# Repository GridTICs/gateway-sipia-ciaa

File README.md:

# Proyecto Final UTN-FRM - Ingeniería Electrónica

_El proyecto se basa en la creación de un gateway que enlaza una red de sensores con un servidor de internet. El README está en su versión beta._ 🚀

_Estas instrucciones te permitirán obtener una copia del proyecto en funcionamiento en tu CIAA para propósitos de desarrollo y pruebas._

*Todo se ha realizado en base al proyecto EDU-CIAA.*

*Se puede encontrar información correspondiente en su página:*

http://www.proyecto-ciaa.com.ar

### Pre-requisitos 📋

> ```
> Tener instalado el "Embedded IDE", GUI de programación de la EDU-CIAA, creada por Martin Ribelotta - El proyecto está creado en dicha aplicación corriendo en Windows 10 x64.
> ```
>

*Dicho software se puede obtener del siguiente link:*

https://github.com/martinribelotta/embedded-ide-builder/releases/tag/v0.6

*En el mismo ya se encuentran las herramientas necesarias para grabar la EDU-CIAA (NXP en mi caso).*

### Instalación 🔧

_Una serie de ejemplos paso a paso que te dice lo que debes ejecutar para tener un entorno de desarrollo ejecutandose_

_Dí cómo será ese paso_

```
Da un ejemplo
```

_Y repite_

```
hasta finalizar
```

_Finaliza con un ejemplo de cómo obtener datos del sistema o como usarlos para una pequeña demo_-

## Ejecutando las pruebas ⚙️

_Explica como ejecutar las pruebas automatizadas para este sistema_

### Analice las pruebas end-to-end 🔩

_Explica que verifican estas pruebas y por qué_

```
Da un ejemplo
```

### Y las pruebas de estilo de codificación ⌨️

_Explica que verifican estas pruebas y por qué_

```
Da un ejemplo
```

## Deployment 📦

_Agrega notas adicionales sobre como hacer deploy_

## Construido con 🛠️

_[CIAA Embedded IDE](https://github.com/martinribelotta/embedded-ide-builder/releases/tag/v0.6) - El IDE de programación utilizado.

## Contribuyendo 🖇️

Por el momento el proyecto es de carácter privado, pero será abierto cuando la versión beta 1.0 esté finalizada.

## Wiki 📖

Puedes encontrar mucho más de cómo utilizar este proyecto en nuestra [Wiki](https://github.com/tu/proyecto/wiki)

## Autores ✒️

_Menciona a todos aquellos que ayudaron a levantar el proyecto desde sus inicios_

* **Lucas Escribano** - [harrylae](https://github.com/harrylae)
* **Rodrigo Gonzalez** 

## Expresiones de Gratitud 🎁

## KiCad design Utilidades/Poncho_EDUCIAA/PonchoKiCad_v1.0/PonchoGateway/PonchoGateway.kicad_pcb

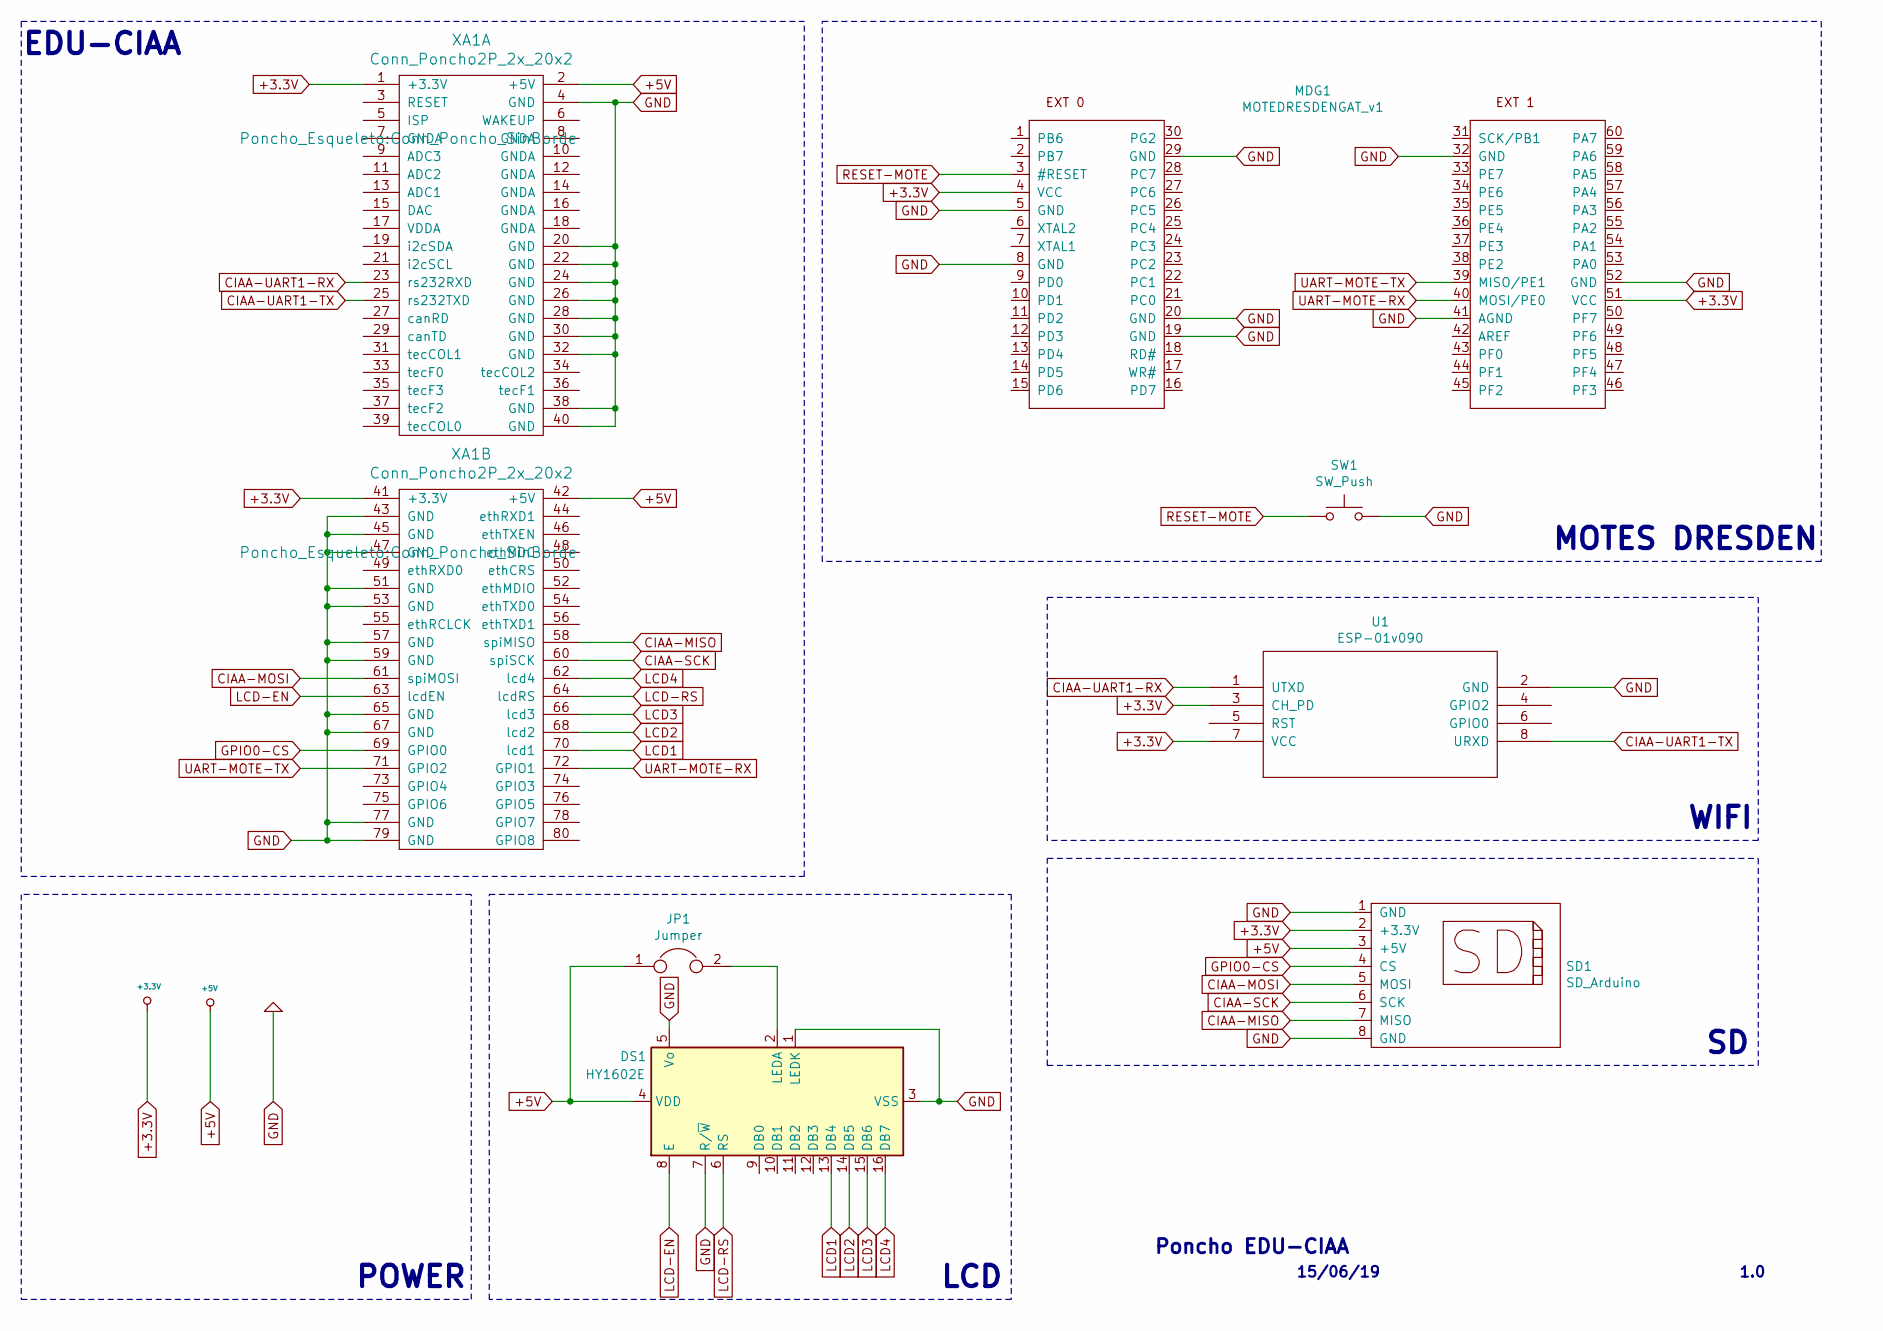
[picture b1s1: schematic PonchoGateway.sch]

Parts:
DS1: HY1602E; Display_Propio
JP1: Jumper; JUMPER-PONCHO-EDU-CIAA
MDG1: MOTEDRESDENGAT_v1; SAMTEC-EDU-CIAA
SD1: SD_Arduino; SD-SHIELD-ARD
SW1: SW_Push; SW_PUSH_6mm
U1: ESP-01v090; ESP-01
XA1: Conn_Poncho2P_2x_20x2; Conn_Poncho_SinBorde

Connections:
+3.3V: MDG1.4 (VCC), MDG1.51 (VCC), SD1.2 (+3.3V), U1.3 (CH_PD), U1.7 (VCC), XA1.1 (+3.3V), XA1.41 (+3.3V)
+5V: DS1.4 (VDD), JP1.1, SD1.3 (+5V), XA1.2 (+5V), XA1.42 (+5V)
CIAA-MISO: SD1.7 (MISO), XA1.58 (spiMISO)
CIAA-MOSI: SD1.5 (MOSI), XA1.61 (spiMOSI)
CIAA-SCK: SD1.6 (SCK), XA1.60 (spiSCK)
CIAA-UART1-RX: U1.1 (UTXD), XA1.23 (rs232RXD)
CIAA-UART1-TX: U1.8 (URXD), XA1.25 (rs232TXD)
GND: DS1.1 (LEDK), DS1.3 (VSS), DS1.5 (Vo), DS1.7 (R/~W), MDG1.5 (GND), MDG1.8 (GND), MDG1.19 (GND), MDG1.20 (GND), MDG1.29 (GND), MDG1.32 (GND), MDG1.41 (AGND), MDG1.52 (GND), SD1.1 (GND), SD1.8 (GND), SW1.2, U1.2 (GND), XA1.4 (GND), XA1.20 (GND), XA1.22 (GND), XA1.24 (GND), XA1.26 (GND), XA1.28 (GND), XA1.30 (GND), XA1.32 (GND), XA1.38 (GND), XA1.40 (GND), XA1.43 (GND), XA1.45 (GND), XA1.47 (GND), XA1.51 (GND), XA1.53 (GND), XA1.57 (GND), XA1.59 (GND), XA1.65 (GND), XA1.67 (GND), XA1.77 (GND), XA1.79 (GND)
GPIO0-CS: SD1.4 (CS), XA1.69 (GPIO0)
LCD1: DS1.13 (DB4), XA1.70 (lcd1)
LCD2: DS1.14 (DB5), XA1.68 (lcd2)
LCD3: DS1.15 (DB6), XA1.66 (lcd3)
LCD4: DS1.16 (DB7), XA1.62 (lcd4)
LCD-EN: DS1.8 (E), XA1.63 (lcdEN)
LCD-RS: DS1.6 (RS), XA1.64 (lcdRS)
unnamed: DS1.2 (LEDA), JP1.2
RESET-MOTE: MDG1.3 (#RESET), SW1.1
UART-MOTE-RX: MDG1.40 (MOSI/PE0), XA1.72 (GPIO1)
UART-MOTE-TX: MDG1.39 (MISO/PE1), XA1.71 (GPIO2)

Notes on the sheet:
MOTES DRESDEN
WIFI
LCD
POWER
EDU-CIAA
Poncho EDU-CIAA
1.0
15/06/19

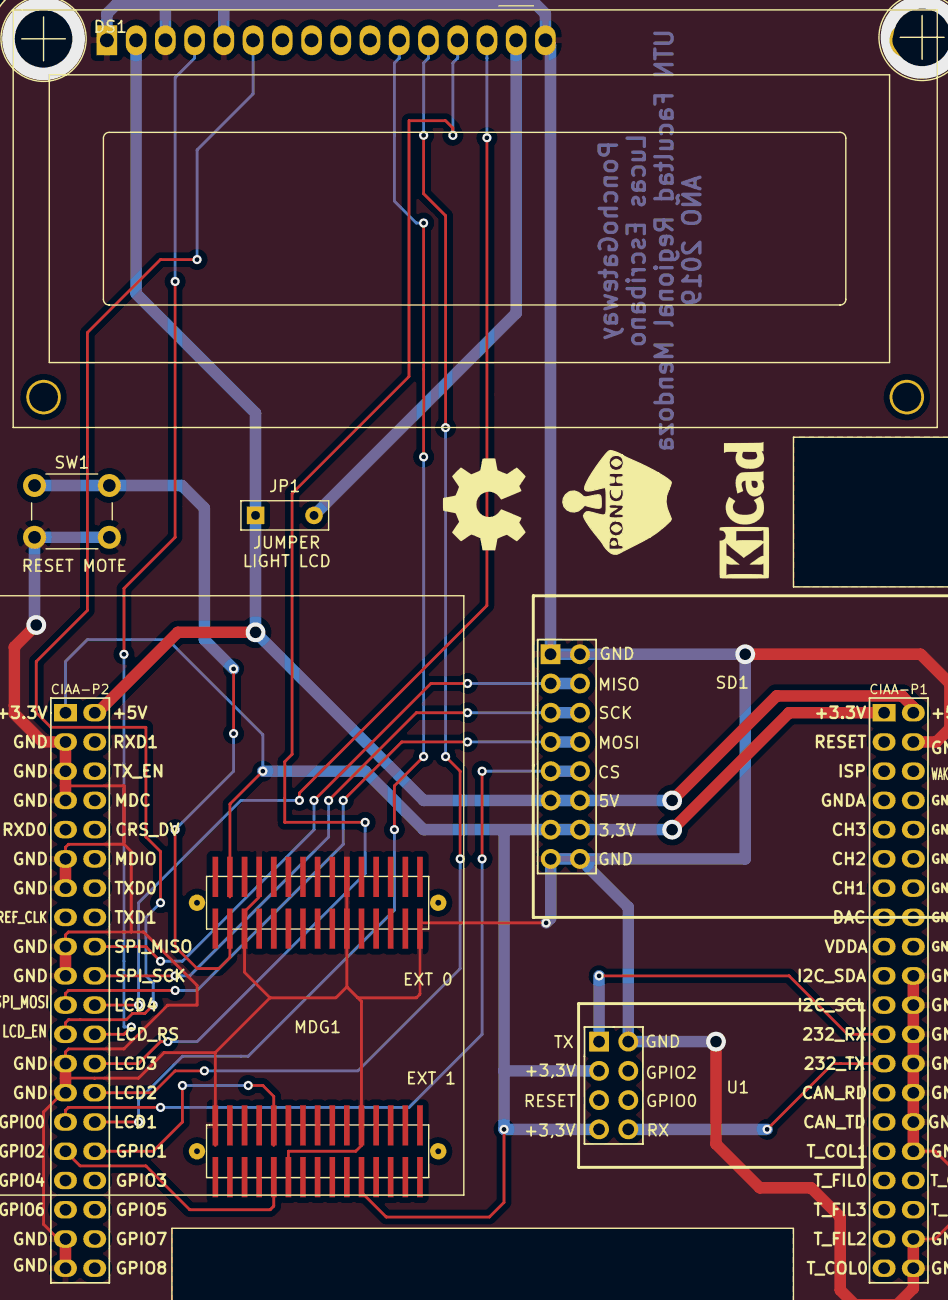
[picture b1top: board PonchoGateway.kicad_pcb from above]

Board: 2 copper layers, 8 parts (0 on the bottom side), 19 nets.

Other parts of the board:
G101: Logo_OSHWA

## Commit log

2019-03-17 First Commit by Lucas Escribano
2019-03-17 Prueba
2019-03-17 Probando Configuraciones de Proyecto Avanzadas
2019-03-17 Actualizando lista de Pendientes...
2019-03-17 Subiendo cambios para cambiar de PC.
2019-03-23 Subiendo cambios en cosas_faltantes.xml
2019-03-24 Cambios en la organización de las carpetas, se agrega el driver FTDI, el programa de SERIAL, se logra la bidireccionalidad.
2019-04-02 Se arregla problema del servidor NTP, la hora se carga correctamente, se deja menues listos en LCD para seguir trabajandoen ellos.
2019-05-22 Subo el informe del proyecto final de la carrera. Falta terminar.
2019-05-22 Subo un Modelo BETA del Readme.md para comenzar a trabajar con el mismo.
2019-05-22 Probando con el Readme.md
2019-05-22 Pude comentar lo que no se debe mostrar. Sigo evaluando el uso de Readme.md
2019-05-22 Siguen las pruebas.
2019-05-22 Readme.md
2019-05-27 Agregando la visibilidad de ESTADOS en el LCD.
2019-05-28 Se agregan los estados iniciales en el LCD, por lo tanto no hace falta estar conectado el puerto serie para saber lo que está sucediendo.
2019-05-28 Se agrega señalización de Estados con los LED RGB (Gpio) de la EDU-CIAA.
2019-05-29 Se realizan cambios en la forma de conexión del ESP para que o se produzcan errores al iniciarlo. Se agrega el Datasheet para utilizarlo si es necesario.
2019-06-07 Se actualizan las cosas faltantes. Se verifica la placa Poncho EDUCIAA.
2019-06-09 Se comienza el desarrollo del PONCHO hardware de la EDU-CIAA Gateway, reemplazando el modelo en Proteus por Kicad.
2019-06-12 Trabajando en el .sch del Poncho Gateway de la EDU-CIAA.
2019-06-16 Arreglo PonchoGateway, corrijo huellas y ubico componentes en la placa final.
2019-06-17 Subo esquemático del ESP8266, y se modifica el PCB de poncho EDU-CIAA-Gateway.
2019-06-18 Se corrige error en esquemático, y se termina el pcb.
2019-06-21 Se agregan Logos en el PonchoGateway, al igual que los power plane referidos a GND en ambas caras.
2019-06-21 Se corrigen problemas en el SCH y PCB. Se realiza última comprobación antes de hacer la placa.
2019-06-21 Imprimo las distintas capas para realizar el PCB.
2019-06-22 Agrego modelo 3D del esp8266, y organizo archivos correctamente.
2019-06-22 Agrego imágenes de vistas 3D para informe.
2019-06-23 Modifico el informe final, agrego contenido, creo referencias, evaluación económica, etc.
2019-06-24 Modificación del README.md
2019-06-25 Actualizo vistas 3D de componentes SD y Jumper.
2019-07-15 Probando la Placa -PonchoGateway-, funciona todo correctamente. Hay que mejorar el software a futuro.
2019-07-17 Ordenando el Repositorio
2019-07-17 Trabajando en el README.md
2019-07-20 Volviendo cambios.
2019-07-20 No recibo mas los datos del NTP por interrupción, sino por funciones propias del UART. - NO FUNCIONA -
2019-07-23 Queda solucionado el problema de servidor NTP.
2019-07-24 Agrego la actualización del informe del proyecto final.
2019-07-24 Se arregla la pasarela Server->Coordinador
2019-07-24 No se arregla el problema con la llegada de datos por UART y el posterior envío al server.
2019-07-24 Se empieza con el Menu por Consola Serie.
2019-07-25 Observamos los datos que llegan desde el Mote, encontramos que el baud rate es de 9600.
2019-07-25 Se crea una máquina de estados para recibir los datos en el UART, se prueban los ISSUES
2019-07-25 Creo interrupción del TIMER_0 para leer los estados de la conexión del SERVER.
2019-07-26 Realicé la función de envío mucho mas esficiente, al igual que la de la recepción.
2019-07-26 Avanzo con el informe final. Agrego la parte del proyecto de GridTics
2019-07-26 Borro archivos innecesarios.
2019-07-27 Cambios en el Informe Final.
2019-07-27 Solucionando los problemas de comunicación bidireccional.
2019-07-27 Trabajando en el Issue #5
2019-07-27 Trabajando en el Issue #6
2019-07-27 Trabajando en el Menu de Configuración. Issue #4
2019-07-27 Armando menu, menu parametros WiFi terminado. Issue #4
2019-07-28 Terminado el menu en consola serie para la configuración de parámetros. Fixes #4
2019-07-29 Trabajando en el Informe. Issue #8
2019-07-30 Termino el infrome final. Creo PDF para imprimir. Fixes #8
2019-07-31 Ordeno carpetas. Empiezo presentación.
2019-08-01 Trabajando en el Issue #3. Muchos errores y no cree branch :-(
2019-08-02 Terminando la presentación y solucionando lo de la SD.
